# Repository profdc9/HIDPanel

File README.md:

# HIDPanel

This is a customizable HID controller for game panels.  The HIDPanel has positions for up to 15 plug in control modules.  These modules can be single buttons, button pairs, rotary encoders, rotary potentiometers, slide potentiometers, and dual axis joysticks (PS4 or Xbox One type replacement joysticks).

The device appears as a USB CDC serial port, a USB HID keyboard, and a USB HID gamepad.  The actions of each module is configured through the serial port.  A command string configures the Keyboard or Gamepad controls to be triggered in response to each action.

# Commands

The commands are sent via the USB CDC serial port terminated by the enter character.  Here are the commands:

SET &lt;module number&gt; &lt;action number&gt; &lt;action command string&gt;

Sets the action command string corresponding to the action number for the given module number (1 to 15).

SHOW &lt;module number&gt;

Shows the current command strings for the module number.  If the module number is zero, show the action strings for all of the modules.

WRITE

Writes the current configuration to flash memory to be restored on power up.

HELP

Display the help (the list of commands).

# Module inputs

Each module has three inputs.  Switch 1, which is a digital only input, switch 2, which is digital or analog, and an analog input, which can be used as a digital or analog input.

The action numbers are:

- 100: Button 1 Pressed (grounded)
- 101: Button 1 Released (high)
- 200: Button 2 Pressed (grounded)
- 201: Button 2 Released (high)
- 300: Analog axis pressed (grounded)
- 301: Analog axis released (high)
- 302: Analog axis moved
- 311: Analog axis position 1/9 (left most)
- 312: Analog axis position 2/9
- 313: Analog axis position 3/9
- 314: Analog axis position 4/9
- 315: Analog axis position 5/9 (center) 
- 316: Analog axis position 6/9
- 317: Analog axis position 7/9
- 318: Analog axis position 8/9
- 319: Analog axis position 9/9 (right most)
- 400: Rotary encoder left
- 401: Rotary encoder right

# Command string

The command string is a sequence of one or two character codes separated by commas.  It should not contain any spaces.  There are three modes.  The mode needs to be selected before the commands for the mode are used.  Multiple modes may be used in the command string by switching between them.  The default is keyboard mode.

- LD: LED Mode
  - Hx: Turn on LED x (x = 1 to 4)
  - Lx: Turn off LED x (x = 1 to 4)
- GP: Gamepad Mode
  - Gx: Set axis x to analog input (x = 1-6, 1=left stick x, 2=left stick y, 3=left stick z, 4=right stick x, 5=right stick y, 6=right stick z)
  - Nx: Set axis x to analog input but reverse the axis
  - Zx: Set axis x to switch 2 analog input
  - Yx: Set axis x to switch 2 analog input but reverse the axis
  - Dx: Set Dpad input to value x (x = 0-8, 0=Centered, 1=Up, 2=Up Right, 3=Right, 4=Down Right, 5=Down, 6=Down Left, 7=Left, 8=Up Left)
  - Hx: Press button x (x=1 to 32)
  - Lx: Release button x
- KB: Keyboard Mode
  - Blank (zero length): keyboard release (two consective commas).
  - LC: Select left control for next key
  - LS: Select left shift for next key
  - LA: Select left alt for next key
  - LG: Select left gui for next key
  - RC: Select right control for next key
  - RS: Select right shift for next key
  - RA: Select right alt for next key
  - RG: Select right gui for next key
  - NK: No key 
  - A-Z: Press key A to Z
  - 0-9: Press key 0 to 9
  - EN: Enter
  - ES: Escape
  - BK: Backspace
  - TB: Tab
  - SP: Space bar
  - -: Minus key
  - =: Equal key
  - [: Left bracket
  - ]: Right bracket
  - \\: Backslash
  - E1: Europe 1
  - E2: Europe 2
  - ; : Semicolon
  - ` : Grave
  - CM: Comma
  - .: Period
  - /: Slash
  - CC: Caps Lock
  - F1-F9: F1 to F9
  - FA: F10 key
  - FB: F11 key
  - FC: F12 Key
  - PS: Print Screen
  - SL: Scroll Lock
  - PA: Pause
  - IN: Insert 
  - HO: Home
  - PU: Page Up
  - DE: Delete
  - ED: End
  - PD: Page Down
  - AR: Arrow Right
  - AL: Arrow Left
  - AD: Arrow Down
  - AU: Arrow Up
  - NL: Num Lock
  - KD: Keypad Divide
  - KM: Keypad Multiple
  - KS: Keypad Subtract
  - KA: Keypad Add
  - KE: Keypad Enter
  - K0-K9: Keypad 0 to 9
  - KL: Keypad Decimal Point
  - KQ: Keypad Equal

Examples:

- KB,LS,H,,E,,L,,L,,O,, : Type the word "HELLO" with the left shift key pressed down during "H" (to capitalize it).
- GP,G2 : Take the analog value of the module and set it to the left stick Y axis.
- GP,D1,D0,D1,D0,D5,D0,D5,D0,D7,D0,D3,D0,D3,D0,H2,L2,H1,L1 : Do combination up,up,down,down,left,right,left,right (on DPad), and then press and release button 2 and then button 1.
- GP,H1,LD,H2 : press button 1, light up LED 2
- KB,F1,GP,H1,LD,L3,GP,L1 : Press keyboard key F1, press button 1 on gamepad, turn off LED 3, release button 1 on gamepad.  Button F1 remains pressed.

Complete commands:

- SET 1 100 KB,A,, : when button 1 on module 1 is pressed, press down the A key
- SET 1 101 KB,, : when button 1 on module 1 is release, release any key
- SET 11 302 GP,G1 : set analog axis of module 11 to axis 1 of the gamepad
- SET 15 302 GP,G2 : set analog axis of module 15 to axis 2 of the gamepad
- SET 11 302 GP,N1 : set analog axis of module 11 to axis 1 of the gamepad, but invert the input
- SET 15 302 GP,N2 : set analog axis of module 15 to axis 2 of the gamepad, but invert the input
- SET 11 100,GP,H4 : when analog stick button is pushed in, press button 4 on gamepad
- SET 11 101,GP,L4 : when analog stick button is released, depress button 4 on gamepad

Pictures:

The following is a pciture of the HIDPanel with different controls in it.  In module 1 is a single push button. In module 3 is a rotary potentiometer, In module 4 is a slide switch.  In module 6 is a rotary encoder.  In module 8 is a push-on push-off button.  Modules 9 and 13 have a digital gamepad.  Modules 10 and 14 have a slide potentiometer.  Modules 11 and 15 have a dual axis joystick.

This is the 3-d printed cover that goes over the HIDPanel.  It is a parametric FreeCAD model and the port openings can be customized in FreeCAD before outputting the cover for the particular modules used.

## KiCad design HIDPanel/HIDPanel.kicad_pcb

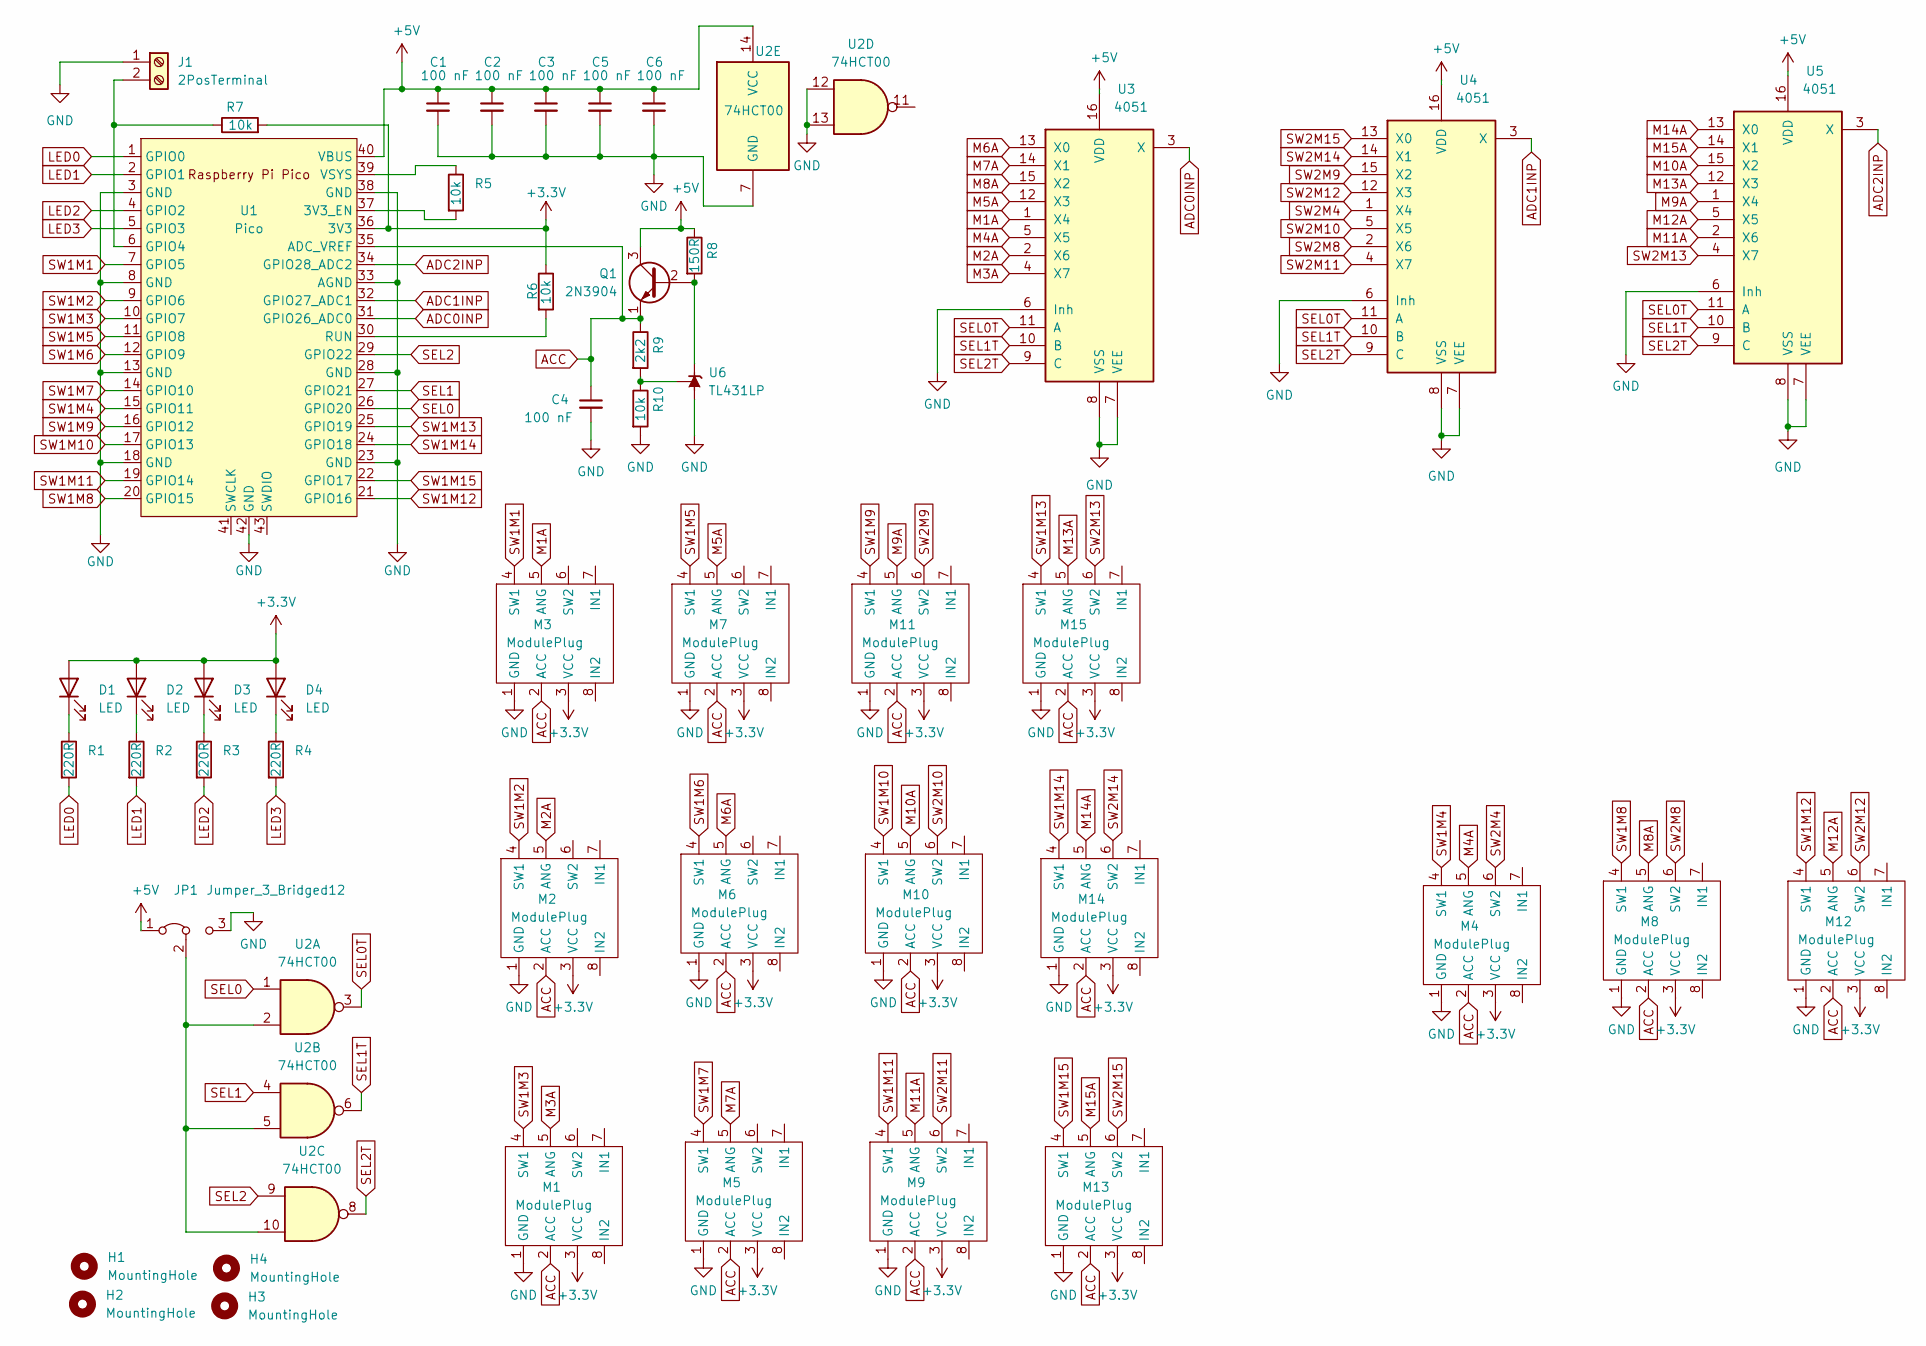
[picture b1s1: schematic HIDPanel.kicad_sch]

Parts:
C1, C2, C3, C4, C5, C6: 100 nF; C_Disc_D5.0mm_W2.5mm_P2.50mm
D1, D2, D3, D4: LED; LED_D3.0mm
H1, H2, H3, H4: MountingHole; MountingHole_3.2mm_M3
J1: 2PosTerminal; PinHeader_1x02_P2.54mm_Vertical
JP1: Jumper_3_Bridged12; SolderJumper-3_P1.3mm_Bridged2Bar12_Pad1.0x1.5mm
M1, M2, M3, M4, M5, M6, M7, M8, M9, M10, M11, M12, M13, M14, M15: ModulePlug
Q1: 2N3904; TO-92_Inline_Wide
R1, R2, R3, R4: 220R; R_Axial_DIN0207_L6.3mm_D2.5mm_P7.62mm_Horizontal
R5, R6, R7, R10: 10k; R_Axial_DIN0207_L6.3mm_D2.5mm_P7.62mm_Horizontal
R8: 150R; R_Axial_DIN0207_L6.3mm_D2.5mm_P7.62mm_Horizontal
R9: 2k2; R_Axial_DIN0207_L6.3mm_D2.5mm_P7.62mm_Horizontal
U1: Pico; RPi_Pico_SMD_TH
U2: 74HCT00; DIP-14_W7.62mm_Socket
U3, U4, U5: 4051; DIP-16_W7.62mm_Socket
U6: TL431LP; TO-92_Inline_Wide

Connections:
+3.3V: D1.2 (A), D2.2 (A), D3.2 (A), D4.2 (A), M1.3 (VCC), M2.3 (VCC), M3.3 (VCC), M4.3 (VCC), M5.3 (VCC), M6.3 (VCC), M7.3 (VCC), M8.3 (VCC), M9.3 (VCC), M10.3 (VCC), M11.3 (VCC), M12.3 (VCC), M13.3 (VCC), M14.3 (VCC), M15.3 (VCC), R6.1, R7.2, U1.36 (3V3)
+5V: C1.1, C2.1, C3.1, C5.1, C6.1, JP1.1 (A), Q1.3 (C), R8.1, U1.40 (VBUS), U2.14 (VCC), U3.16 (VDD), U4.16 (VDD), U5.16 (VDD)
ACC: C4.1, M1.2 (ACC), M2.2 (ACC), M3.2 (ACC), M4.2 (ACC), M5.2 (ACC), M6.2 (ACC), M7.2 (ACC), M8.2 (ACC), M9.2 (ACC), M10.2 (ACC), M11.2 (ACC), M12.2 (ACC), M13.2 (ACC), M14.2 (ACC), M15.2 (ACC), Q1.1 (E), R9.1, U1.35 (ADC_VREF)
ADC0INP: U1.31 (GPIO26_ADC0), U3.3 (X)
ADC1INP: U1.32 (GPIO27_ADC1), U4.3 (X)
ADC2INP: U1.34 (GPIO28_ADC2), U5.3 (X)
GND: C1.2, C2.2, C3.2, C4.2, C5.2, C6.2, J1.1, JP1.3 (B), M1.1 (GND), M2.1 (GND), M3.1 (GND), M4.1 (GND), M5.1 (GND), M6.1 (GND), M7.1 (GND), M8.1 (GND), M9.1 (GND), M10.1 (GND), M11.1 (GND), M12.1 (GND), M13.1 (GND), M14.1 (GND), M15.1 (GND), R10.2, U1.3 (GND), U1.8 (GND), U1.13 (GND), U1.18 (GND), U1.23 (GND), U1.28 (GND), U1.33 (AGND), U1.38 (GND), U1.42 (GND), U2.7 (GND), U2.12, U2.13, U3.6 (Inh), U3.7 (VEE), U3.8 (VSS), U4.6 (Inh), U4.7 (VEE), U4.8 (VSS), U5.6 (Inh), U5.7 (VEE), U5.8 (VSS), U6.2 (A)
LED0: R1.2, U1.1 (GPIO0)
LED1: R2.2, U1.2 (GPIO1)
LED2: R3.2, U1.4 (GPIO2)
LED3: R4.2, U1.5 (GPIO3)
M1A: M3.5 (ANG), U3.1 (X4)
M2A: M2.5 (ANG), U3.2 (X6)
M3A: M1.5 (ANG), U3.4 (X7)
M4A: M4.5 (ANG), U3.5 (X5)
M5A: M7.5 (ANG), U3.12 (X3)
M6A: M6.5 (ANG), U3.13 (X0)
M7A: M5.5 (ANG), U3.14 (X1)
M8A: M8.5 (ANG), U3.15 (X2)
M9A: M11.5 (ANG), U5.1 (X4)
M10A: M10.5 (ANG), U5.15 (X2)
M11A: M9.5 (ANG), U5.2 (X6)
M12A: M12.5 (ANG), U5.5 (X5)
M13A: M15.5 (ANG), U5.12 (X3)
M14A: M14.5 (ANG), U5.13 (X0)
M15A: M13.5 (ANG), U5.14 (X1)
unnamed: D1.1 (K), R1.1
unnamed: D2.1 (K), R2.1
unnamed: D3.1 (K), R3.1
unnamed: D4.1 (K), R4.1
unnamed: J1.2, R7.1, U1.6 (GPIO4)
unnamed: Q1.2 (B), R8.2, U6.3 (K)
unnamed: R5.1, U1.39 (VSYS)
unnamed: R5.2, U1.37 (3V3_EN)
unnamed: R6.2, U1.30 (RUN)
unnamed: R9.2, R10.1, U6.1 (REF)
unnamed: JP1.2 (C), U2.2, U2.5, U2.10
SEL0: U1.26 (GPIO20), U2.1
SEL0T: U2.3, U3.11 (A), U4.11 (A), U5.11 (A)
SEL1: U1.27 (GPIO21), U2.4
SEL1T: U2.6, U3.10 (B), U4.10 (B), U5.10 (B)
SEL2: U1.29 (GPIO22), U2.9
SEL2T: U2.8, U3.9 (C), U4.9 (C), U5.9 (C)
SW1M1: M3.4 (SW1), U1.7 (GPIO5)
SW1M2: M2.4 (SW1), U1.9 (GPIO6)
SW1M3: M1.4 (SW1), U1.10 (GPIO7)
SW1M4: M4.4 (SW1), U1.15 (GPIO11)
SW1M5: M7.4 (SW1), U1.11 (GPIO8)
SW1M6: M6.4 (SW1), U1.12 (GPIO9)
SW1M7: M5.4 (SW1), U1.14 (GPIO10)
SW1M8: M8.4 (SW1), U1.20 (GPIO15)
SW1M9: M11.4 (SW1), U1.16 (GPIO12)
SW1M10: M10.4 (SW1), U1.17 (GPIO13)
SW1M11: M9.4 (SW1), U1.19 (GPIO14)
SW1M12: M12.4 (SW1), U1.21 (GPIO16)
SW1M13: M15.4 (SW1), U1.25 (GPIO19)
SW1M14: M14.4 (SW1), U1.24 (GPIO18)
SW1M15: M13.4 (SW1), U1.22 (GPIO17)
SW2M4: M4.6 (SW2), U4.1 (X4)
SW2M8: M8.6 (SW2), U4.2 (X6)
SW2M9: M11.6 (SW2), U4.15 (X2)
SW2M10: M10.6 (SW2), U4.5 (X5)
SW2M11: M9.6 (SW2), U4.4 (X7)
SW2M12: M12.6 (SW2), U4.12 (X3)
SW2M13: M15.6 (SW2), U5.4 (X7)
SW2M14: M14.6 (SW2), U4.14 (X1)
SW2M15: M13.6 (SW2), U4.13 (X0)

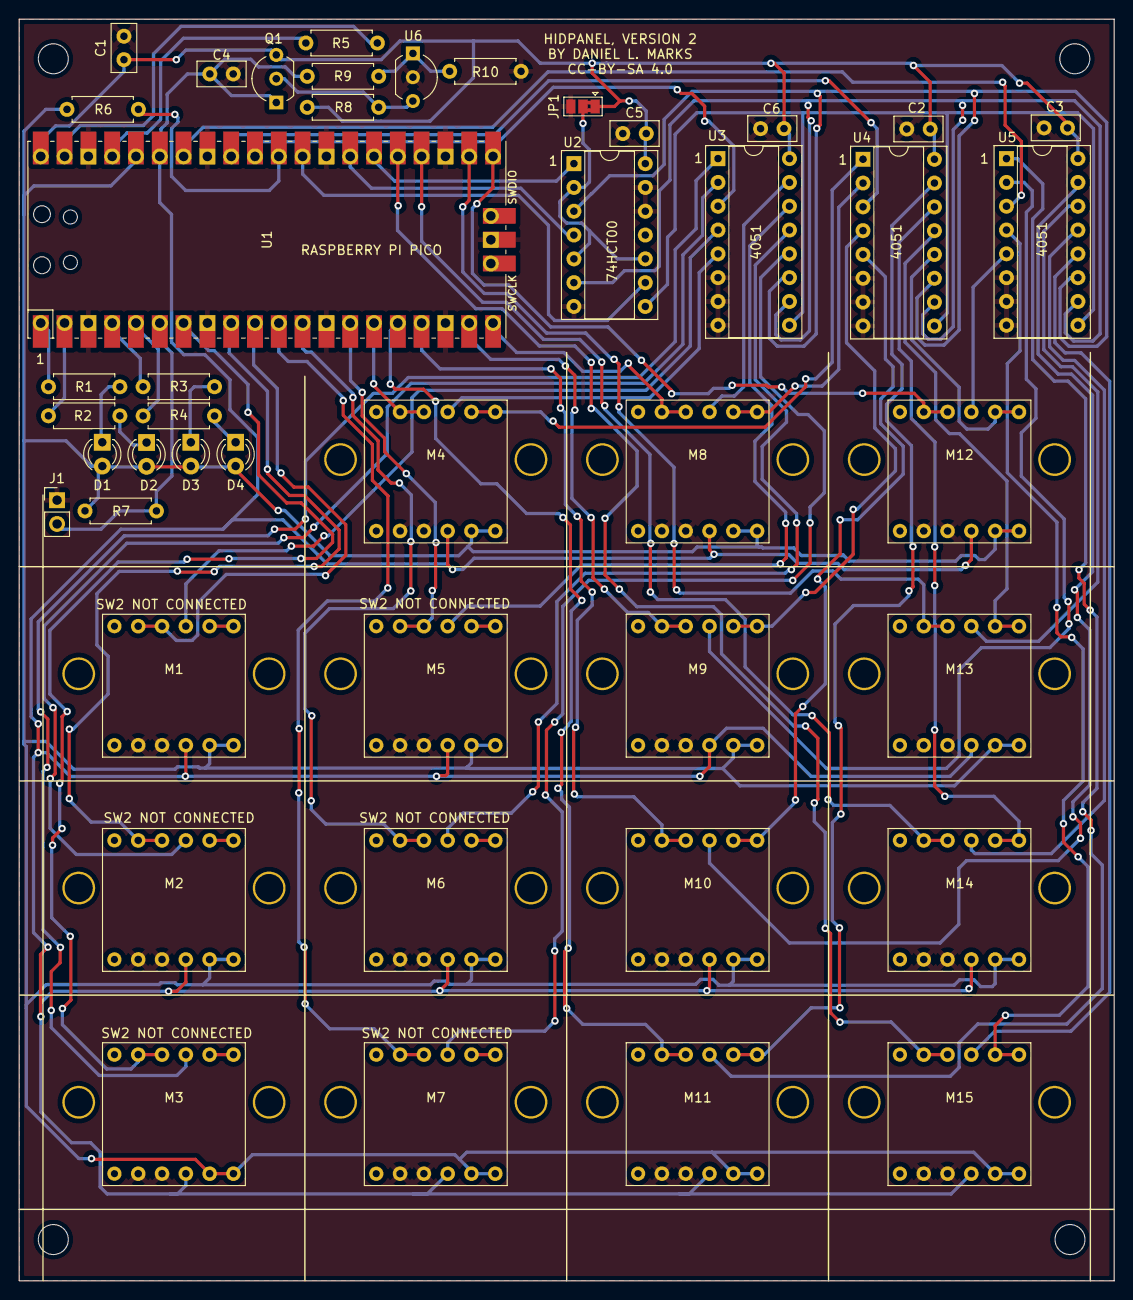
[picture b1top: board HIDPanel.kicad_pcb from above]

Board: 2 copper layers, 116.8 x 134.6 mm, 48 parts (0 on the bottom side), 67 nets.

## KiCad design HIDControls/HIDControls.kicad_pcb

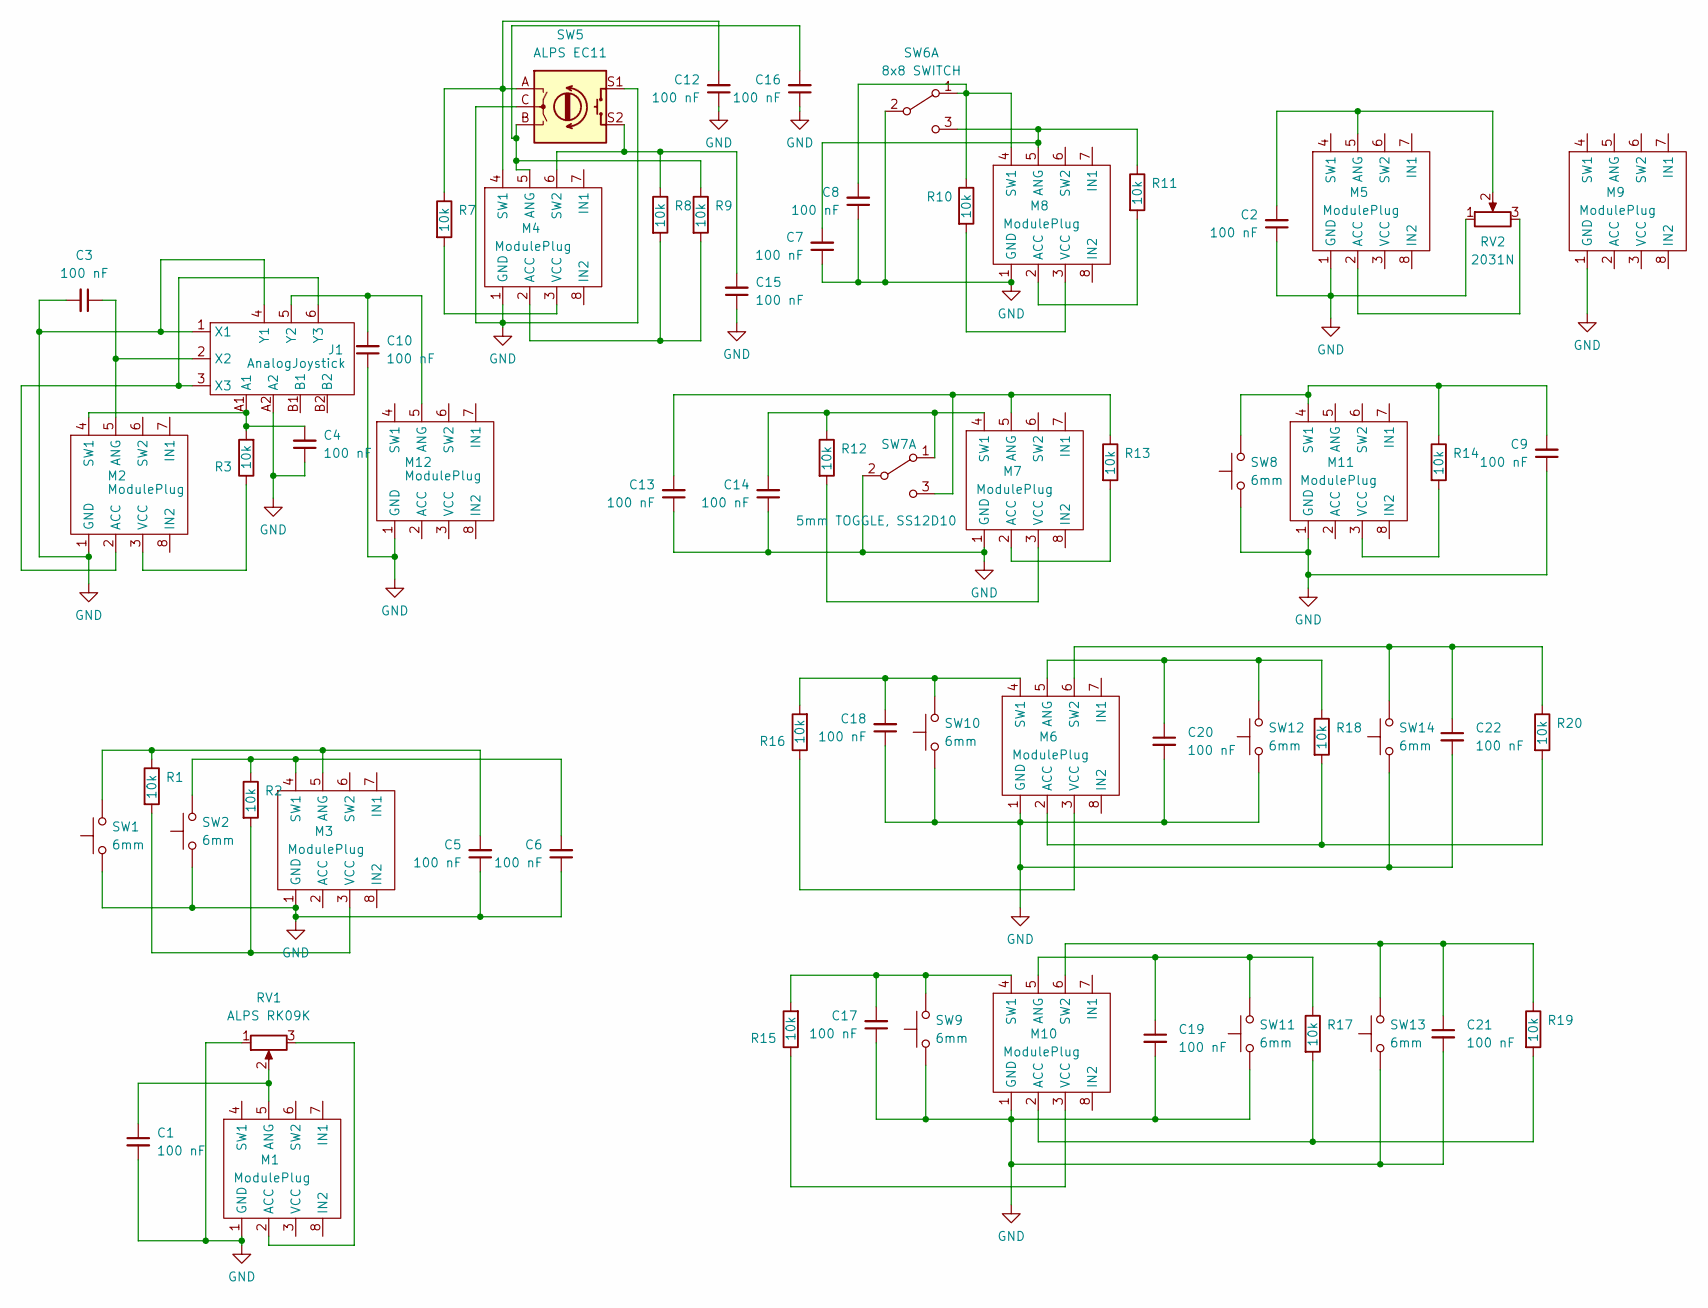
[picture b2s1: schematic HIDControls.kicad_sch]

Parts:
C1, C2, C3, C4, C5, C6, C7, C8, C9, C10, C12, C13, C14, C15, C16, C17, C18, C19, C20, C21, C22: 100 nF; C_Disc_D5.0mm_W2.5mm_P2.50mm
J1: AnalogJoystick
M1, M3, M4, M7, M8, M11: ModulePlug
M2, M5, M6: ModulePlug; LeftPartModulePlug
M9, M10, M12: ModulePlug; RightPartModulePlug
R1, R2, R3, R7, R8, R9, R10, R11, R12, R13, R14, R15, R16, R17, R18, R19, R20: 10k; R_Axial_DIN0207_L6.3mm_D2.5mm_P7.62mm_Horizontal
RV1: ALPS RK09K; Potentiometer_Alps_RK09K_Single_Vertical
RV2: 2031N; Linear-Pot-2031N
SW1, SW2, SW8, SW9, SW10, SW11, SW12, SW13, SW14: 6mm; SW_PUSH_6mm
SW5: ALPS EC11; RotaryEncoder_Alps_EC11E-Switch_Vertical_H20mm
SW6: 8x8 SWITCH; SW_Push_2P2T_Toggle_CK_PVA2xxH1xxxxxxV2
SW7: 5mm TOGGLE, SS12D10; 5mmSPDTtoggle

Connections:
GND: C1.2, C2.1, C3.2, C4.1, C5.1, C6.1, C7.1, C8.1, C9.1, C10.1, C12.1, C13.1, C14.1, C15.1, C16.1, C17.1, C18.1, C19.2, C20.2, C21.2, C22.2, J1.1 (X1), J1.4 (Y1), J1.A2, M1.1 (GND), M2.1 (GND), M3.1 (GND), M4.1 (GND), M5.1 (GND), M6.1 (GND), M7.1 (GND), M8.1 (GND), M9.1 (GND), M10.1 (GND), M11.1 (GND), M12.1 (GND), RV1.1, RV2.1, SW1.1, SW2.1, SW5.C, SW5.S1, SW6.2 (B), SW7.2 (B), SW8.1, SW9.1, SW10.1, SW11.1, SW12.1, SW13.1, SW14.1
unnamed: C1.1, M1.5 (ANG), RV1.2
unnamed: C2.2, M5.5 (ANG), RV2.2
unnamed: C3.1, J1.2 (X2), M2.5 (ANG)
unnamed: C4.2, J1.A1, M2.4 (SW1), R3.2
unnamed: C5.2, M3.5 (ANG), R1.1, SW1.2
unnamed: C6.2, M3.4 (SW1), R2.1, SW2.2
unnamed: C7.2, M8.5 (ANG), R11.1, SW6.3 (C)
unnamed: C8.2, M8.4 (SW1), R10.1, SW6.1 (A)
unnamed: C9.2, M11.4 (SW1), R14.1, SW8.2
unnamed: C10.2, J1.5 (Y2), M12.5 (ANG)
unnamed: C12.2, M4.4 (SW1), R7.1, SW5.A
unnamed: C13.2, M7.5 (ANG), R13.1, SW7.3 (C)
unnamed: C14.2, M7.4 (SW1), R12.1, SW7.1 (A)
unnamed: C15.2, M4.6 (SW2), R8.1, SW5.S2
unnamed: C16.2, M4.5 (ANG), R9.1, SW5.B
unnamed: C17.2, M10.4 (SW1), R15.2, SW9.2
unnamed: C18.2, M6.4 (SW1), R16.2, SW10.2
unnamed: C19.1, M10.5 (ANG), R17.1, SW11.2
unnamed: C20.1, M6.5 (ANG), R18.1, SW12.2
unnamed: C21.1, M10.6 (SW2), R19.1, SW13.2
unnamed: C22.1, M6.6 (SW2), R20.1, SW14.2
unnamed: J1.3 (X3), J1.6 (Y3), M2.2 (ACC)
unnamed: M1.2 (ACC), RV1.3
unnamed: M2.3 (VCC), R3.1
unnamed: M3.3 (VCC), R1.2, R2.2
unnamed: M4.2 (ACC), R8.2, R9.2
unnamed: M4.3 (VCC), R7.2
unnamed: M5.2 (ACC), RV2.3
unnamed: M6.2 (ACC), R18.2, R20.2
unnamed: M6.3 (VCC), R16.1
unnamed: M7.2 (ACC), R13.2
unnamed: M7.3 (VCC), R12.2
unnamed: M8.2 (ACC), R11.2
unnamed: M8.3 (VCC), R10.2
unnamed: M10.2 (ACC), R17.2, R19.2
unnamed: M10.3 (VCC), R15.1
unnamed: M11.3 (VCC), R14.2

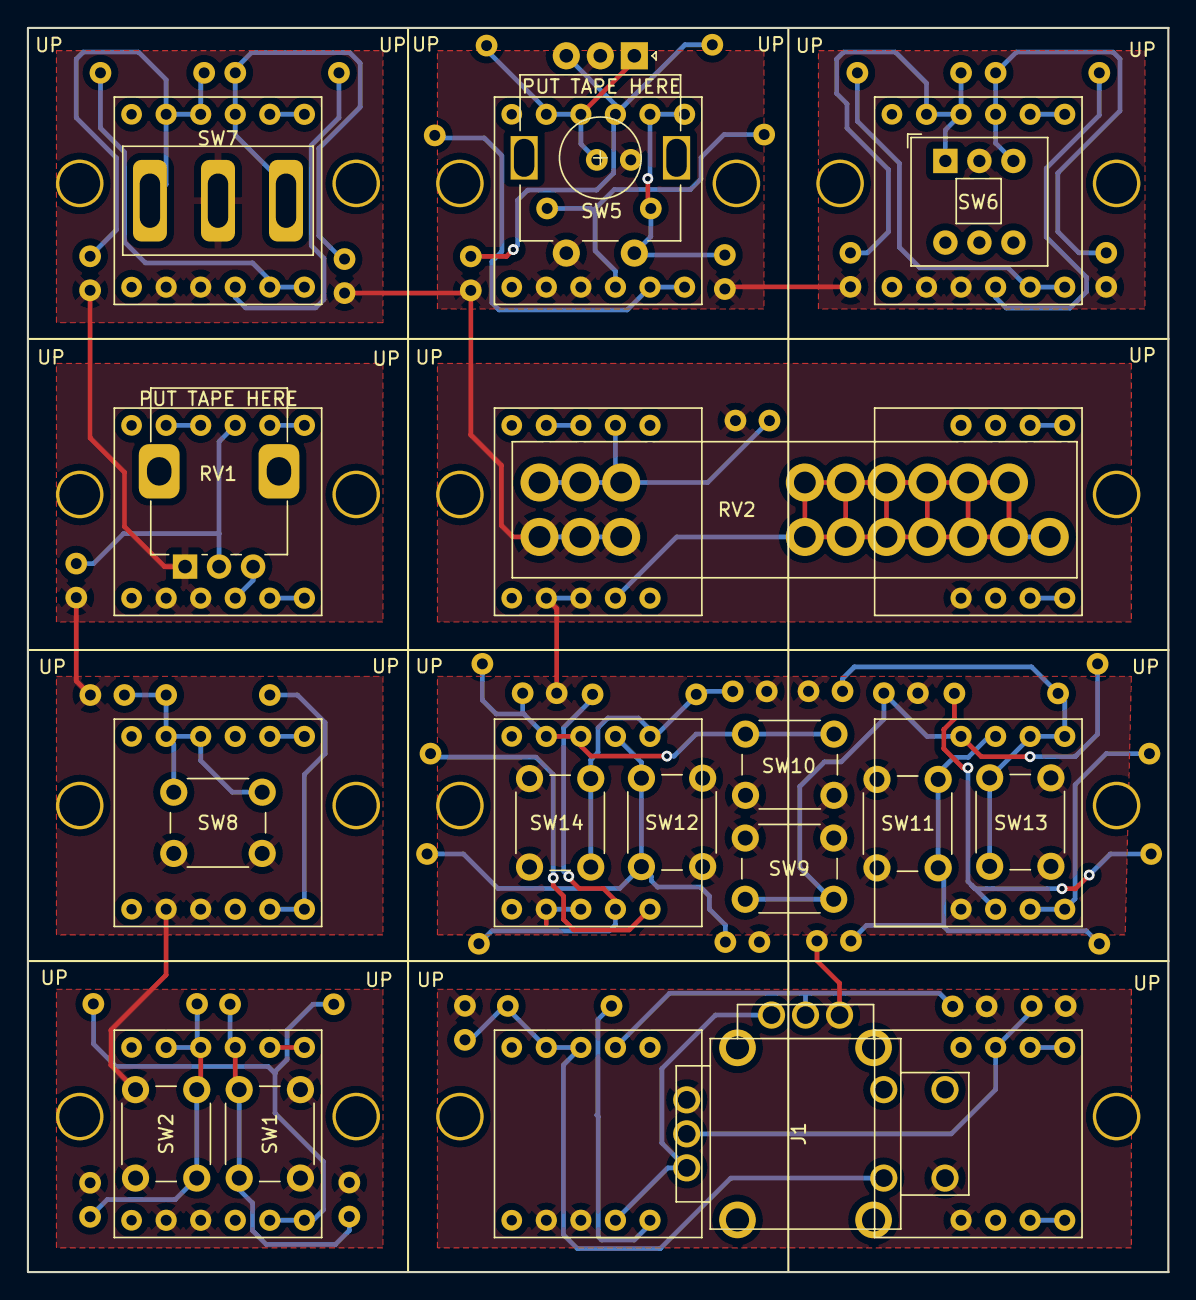
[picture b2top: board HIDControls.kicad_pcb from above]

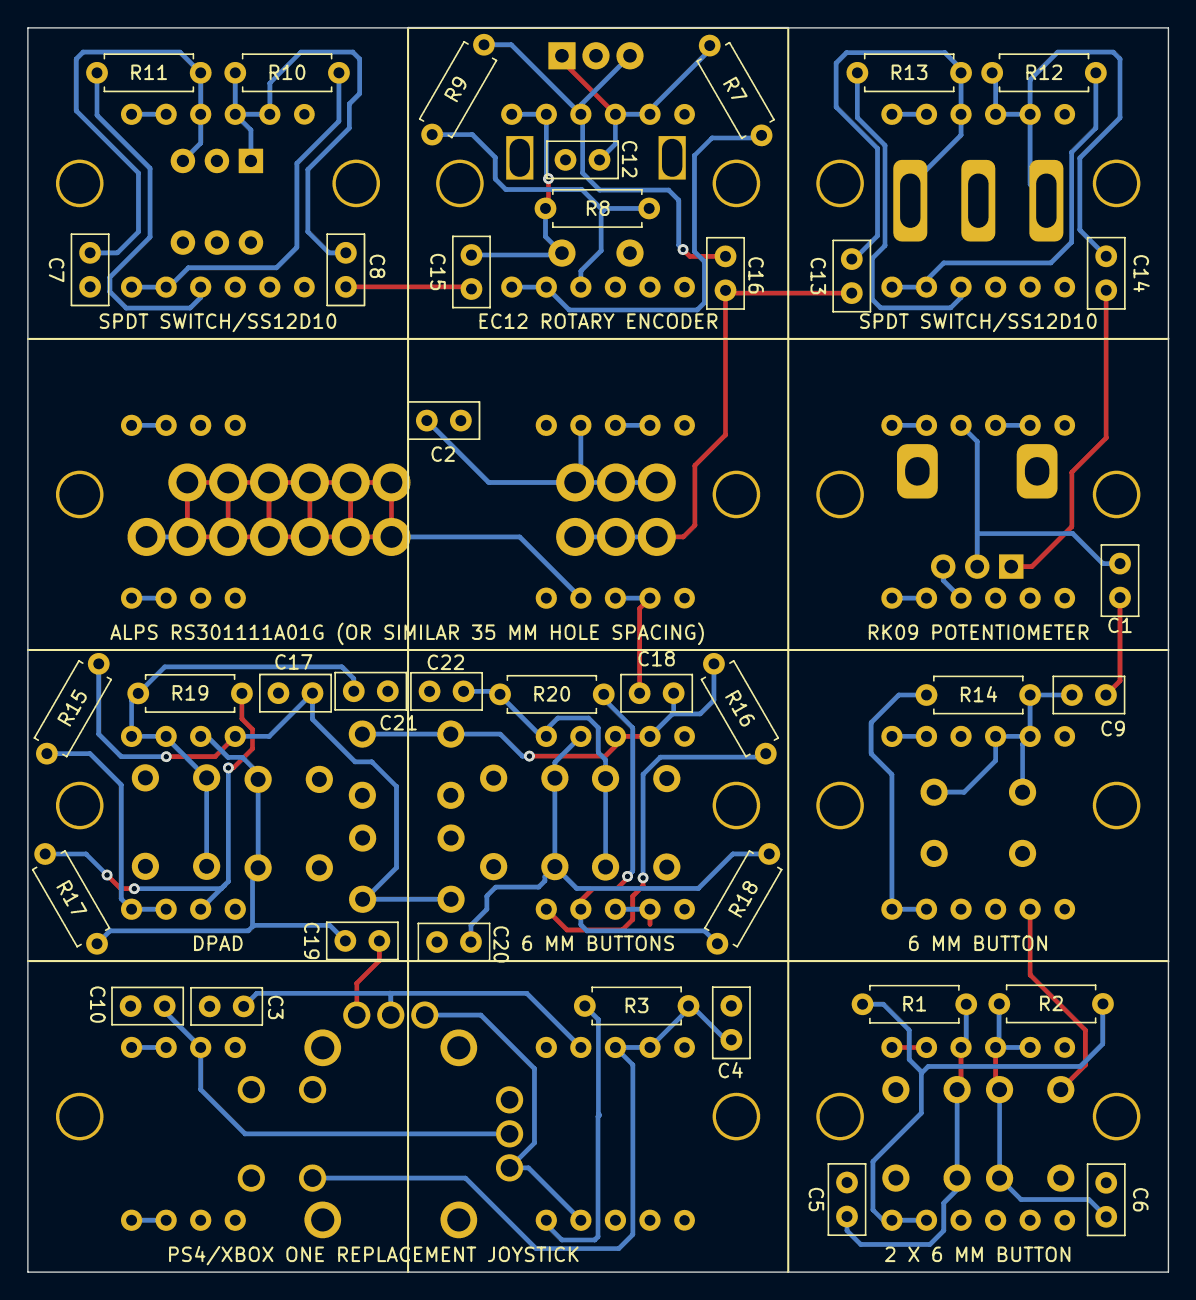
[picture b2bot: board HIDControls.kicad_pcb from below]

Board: 2 copper layers, 83.8 x 91.4 mm, 65 parts (38 on the bottom side), 38 nets.

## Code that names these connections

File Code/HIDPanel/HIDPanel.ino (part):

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
#define INPUT_SELECT_INVERTED 1

#define LED0 0
#define LED1 1
#define LED2 2
#define LED3 3

#define SEL0 20
#define SEL1 21
#define SEL2 22

#define ADC0INP A0
#define ADC1INP A1
#define ADC2INP A2

#define TIMER_INTERRUPT_DEBUG         0
#define _TIMERINTERRUPT_LOGLEVEL_     0
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   usb_hid.begin();
   Serial.begin(9600);
   console_setMainSerial(&Serial);
   pinMode(SEL0, OUTPUT);
   pinMode(SEL1, OUTPUT);
   pinMode(SEL2, OUTPUT);
   pinMode(LED0, OUTPUT);
   pinMode(LED1, OUTPUT);
   pinMode(LED2, OUTPUT);
   pinMode(LED3, OUTPUT);
   pinMode(ADC0INP, INPUT);
   pinMode(ADC1INP, INPUT);
   pinMode(ADC2INP, INPUT);
   for (uint8_t i=5;i<20;i++) pinMode(i, INPUT);
   analogReadResolution(16);
   digitalWrite(LED0, HIGH);
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
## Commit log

2023-02-20 Tweaked some distances
2023-02-20 Spaced out plugin footprint bigger
2023-02-20 Added HIDControls
2023-02-21 Minor layout tweaks
2023-02-21 Added AnalogJoystick
2023-02-21 Added analog joystick device
2023-02-22 JLCPCB order 2023-22-02
2023-02-22 Oops 74HCT32 not 74HCT08
2023-02-23 Added CAD cover
2023-02-26 Created example CDC,HID Keyboard,HID Gamepad device
2023-02-26 Added ascii to keyboard translation
2023-02-26 Added timer interrupt
2023-02-28 Initial draft of firmware
2023-02-28 Documentation
2023-03-01 Eliminated some code that shouldn't be ther
2023-03-13 Added CAD models
2023-03-16 Working buttons, encoders
2023-03-16 Remove RPi Timers (not needed)
2023-03-16 Fixed update problem
2023-03-17 Fixed minor bugs
2023-03-17 Modified README.md
2023-03-18 Rev 2 HIDPanel board
2023-03-18 Modified HIDControls to include labels of parts
2023-03-18 Separate fills for each control
2023-03-19 A few layout tweaks
2023-04-21 Added reinforcement for standoffs
2023-06-19 Added new pictures

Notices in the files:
Code/HIDPanel/HIDPanel.ino:
Copyright (c) 2023 Daniel Marks
HIDPanel/HIDPanel.kicad_pcb:
CC-BY-SA 4.0
